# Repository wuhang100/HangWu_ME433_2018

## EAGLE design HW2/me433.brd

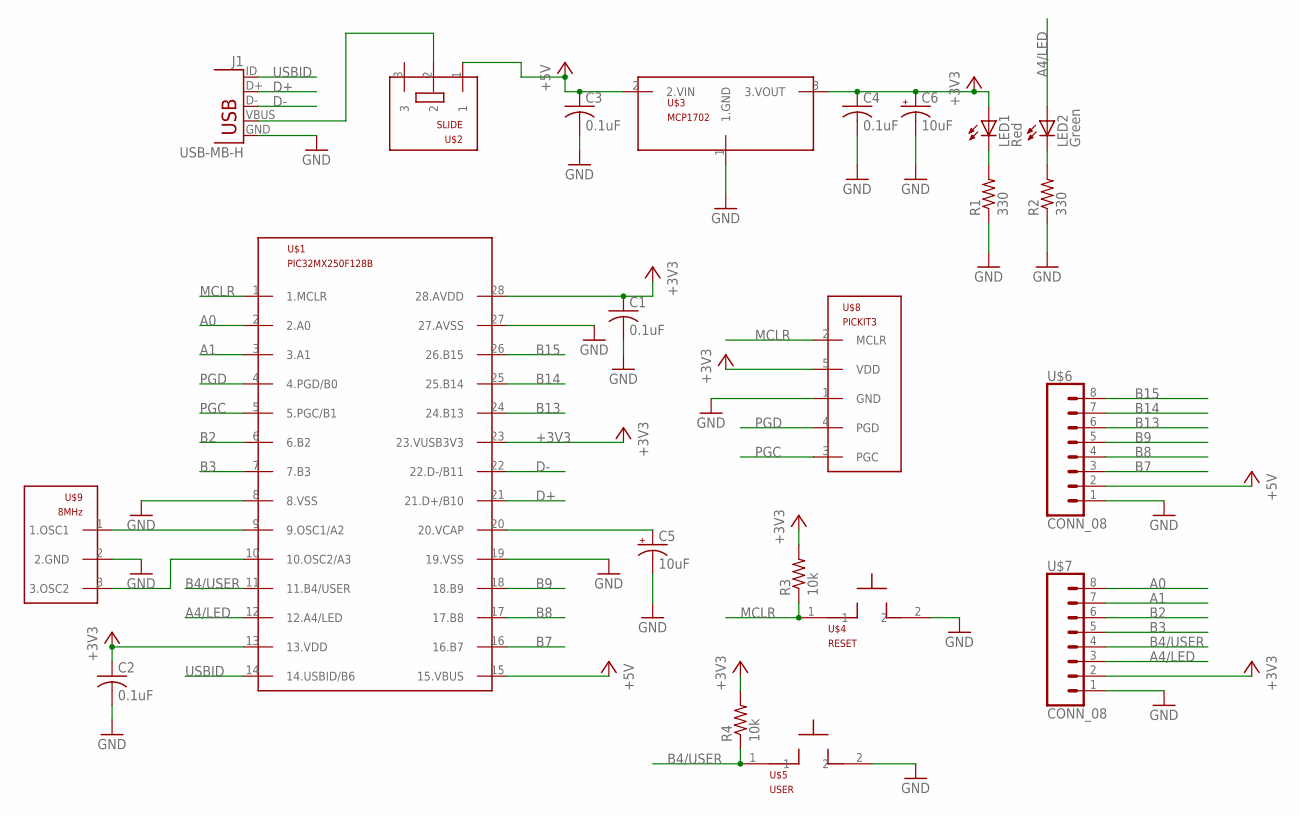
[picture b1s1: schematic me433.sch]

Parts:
C1, C2, C3, C4: 0.1uF; C025-025X050
C5, C6: 10uF; B45181B
J1: USB-MB-H
LED1: Red; LED3MM
LED2: Green; LED3MM
R1, R2: 330; 0207/10
R3, R4: 10k; 0207/10
U$1: PIC32MX250F128B; DIL28-3
U$2: SLIDE
U$3: MCP1702; TO92
U$4: RESET; PB
U$5: USER; PB
U$6, U$7: CONN_08; 1X08
U$8: PICKIT3; 1X05
U$9: 8MHz; OSC

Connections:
+3V3: C1.1, C2.1, C4.1, C6.+, LED1.A, R3.2, R4.2, U$1.13 (13.VDD), U$1.23 (23.VUSB3V3), U$1.28 (28.AVDD), U$3.3 (3.VOUT), U$7.2, U$8.5 (VDD)
+5V: C3.1, U$1.15 (15.VBUS), U$2.1, U$3.2 (2.VIN), U$6.2
A0: U$1.2 (2.A0), U$7.8
A1: U$1.3 (3.A1), U$7.7
A4/LED: LED2.A, U$1.12 (12.A4/LED), U$7.3
B2: U$1.6 (6.B2), U$7.6
B3: U$1.7 (7.B3), U$7.5
B4/USER: R4.1, U$1.11 (11.B4/USER), U$5.1, U$7.4
B7: U$1.16 (16.B7), U$6.3
B8: U$1.17 (17.B8), U$6.4
B9: U$1.18 (18.B9), U$6.5
B13: U$1.24 (24.B13), U$6.6
B14: U$1.25 (25.B14), U$6.7
B15: U$1.26 (26.B15), U$6.8
D+: J1.D+, U$1.21 (21.D+/B10)
D-: J1.D-, U$1.22 (22.D-/B11)
GND: C1.2, C2.2, C3.2, C4.2, C5.-, C6.-, J1.GND, R1.1, R2.1, U$1.8 (8.VSS), U$1.19 (19.VSS), U$1.27 (27.AVSS), U$3.1 (1.GND), U$4.2, U$5.2, U$6.1, U$7.1, U$8.1 (GND), U$9.2 (2.GND)
MCLR: R3.1, U$1.1 (1.MCLR), U$4.1, U$8.2 (MCLR)
unnamed: J1.VBUS, U$2.2
unnamed: LED2.K (C), R2.2
unnamed: LED1.K (C), R1.2
unnamed: U$1.9 (9.OSC1/A2), U$9.1 (1.OSC1)
unnamed: U$1.10 (10.OSC2/A3), U$9.3 (3.OSC2)
unnamed: C5.+, U$1.20 (20.VCAP)
PGC: U$1.5 (5.PGC/B1), U$8.3 (PGC)
PGD: U$1.4 (4.PGD/B0), U$8.4 (PGD)
USBID: J1.ID, U$1.14 (14.USBID/B6)

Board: 2 copper layers, 22 parts (0 on the bottom side), 27 nets, no tracks yet.

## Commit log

2018-04-09 HW1_1
2018-04-09 HW1_2
2018-04-10 photos
2018-04-10 others
2018-04-17 Create HW3
2018-04-17 Create ME433 HW3
2018-04-24 Create main
2018-04-24 Update main
2018-04-30 Create read me
2018-05-10 This is actually homework 10.
2018-05-28 test
2018-05-28 HW15 android
2018-05-28 HW15
    android
2018-05-28 PIC code
2018-05-28 android
2018-05-28 android camera
2018-06-04 homework
2018-06-12 reupload the whole project
2018-06-12 I modify the code of HW14
2018-06-12 I borrowed the code from HW14
2018-06-12 HW17
2018-06-12 hw18
2018-06-12 video upload
2018-06-14 add spurce code
